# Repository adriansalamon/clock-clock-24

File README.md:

## My own ClockClock 24 replica

My own take/version of the ClockClock 24 by [Humans Since 1982](https://www.humanssince1982.com) - A digital clock made from 24 analog clocks.
All credit goes to them for coming up with such an awesome design.

My version is made 100% from scratch using my own hardware design.
Mine is also slightly smaller, made to fit perfectly on my shelf.
This design uses 6 Arduino nanos, each in control of 4 individual
clocks, and an ESP32 which orchestrates and sends commands to all
Arduinos.

The physical clock is made from MDF, which was routed using a 3d
printed jig (I don't own a CNC). That process will not be published.

The software is still WIP and not finished.

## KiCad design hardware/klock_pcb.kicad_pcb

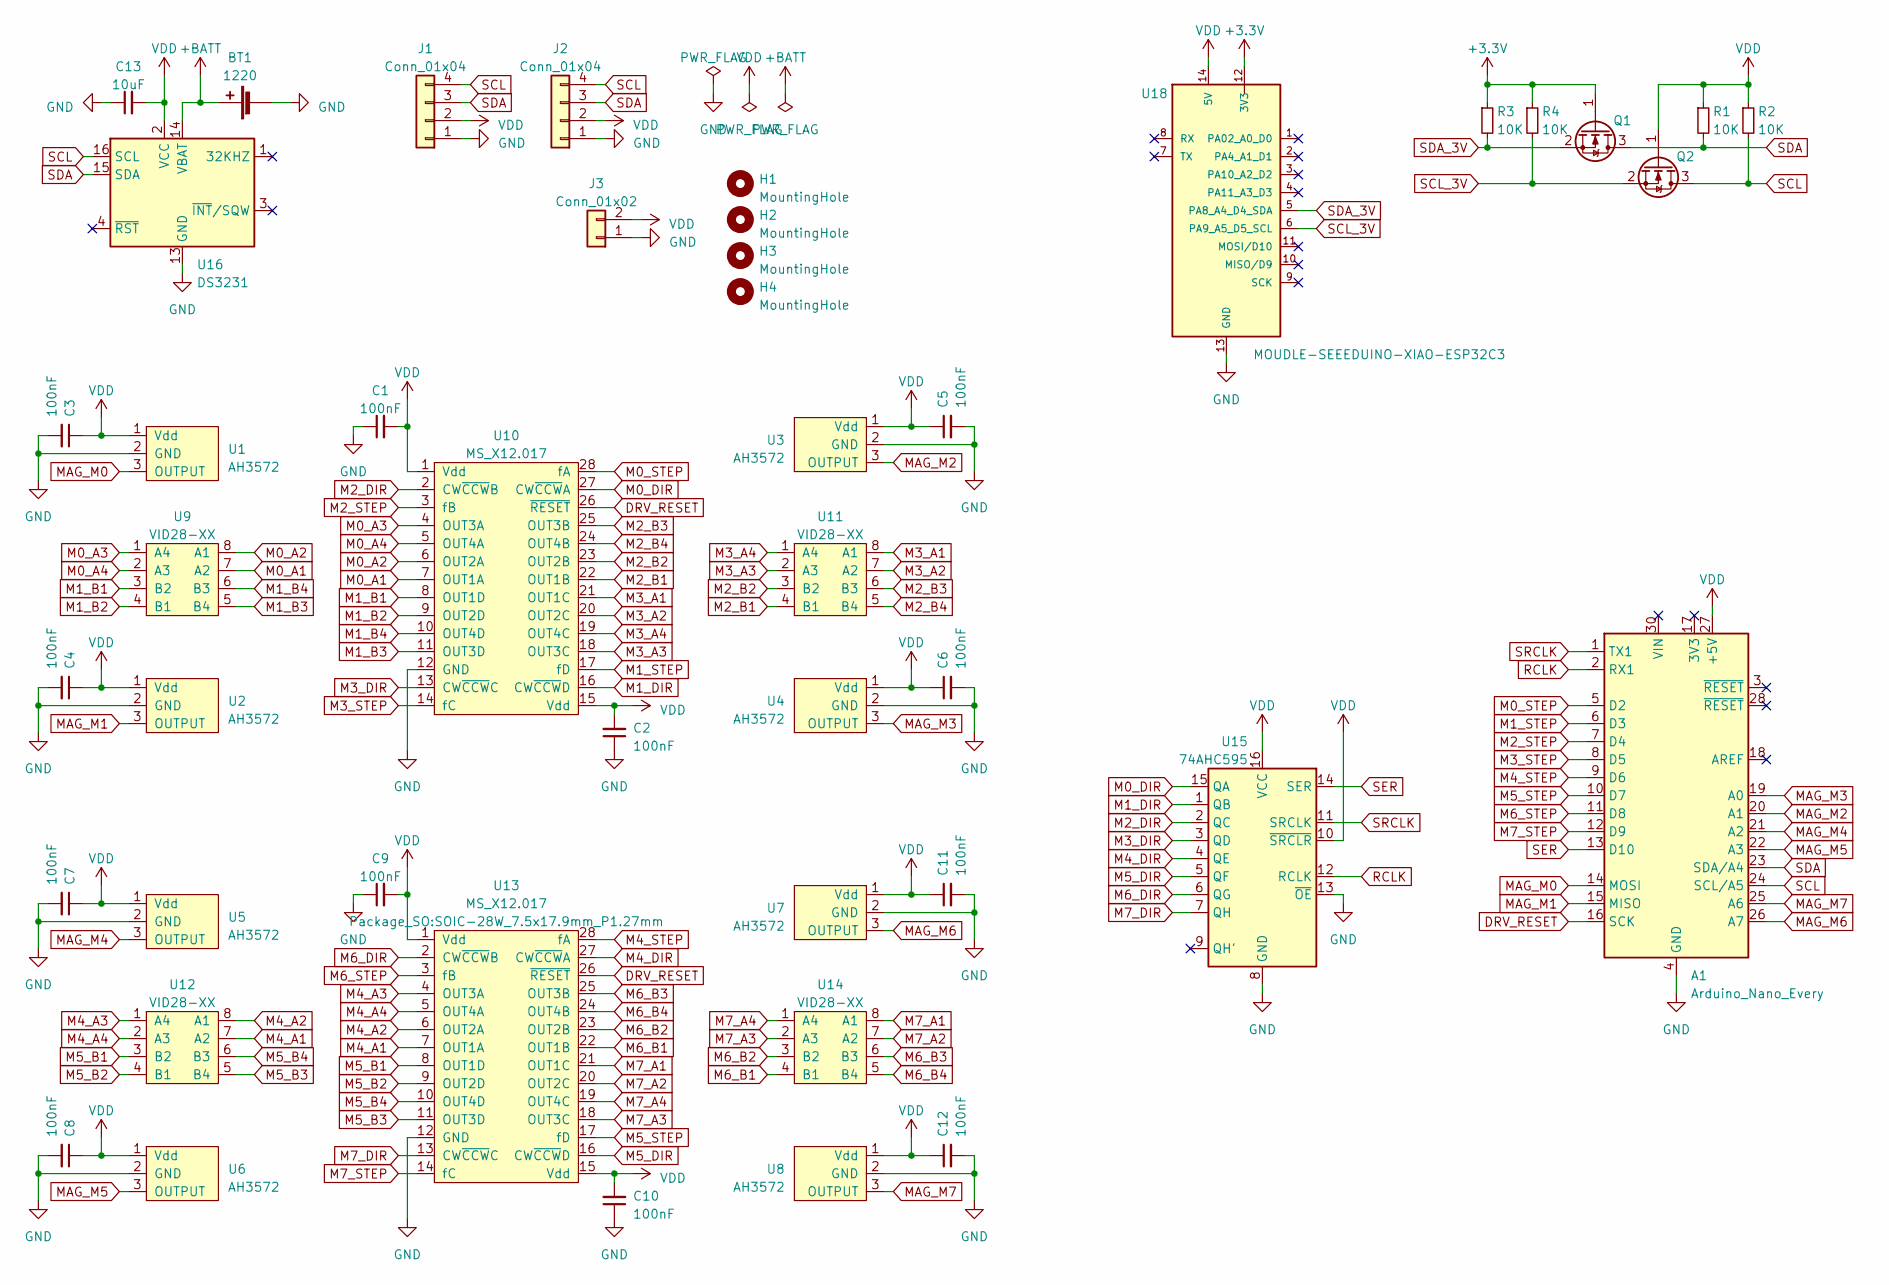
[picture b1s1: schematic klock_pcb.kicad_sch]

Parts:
A1: Arduino_Nano_Every; Arduino_Nano
BT1: 1220; BatteryHolder_Keystone_3001_1x12mm
C1, C2, C3, C4, C5, C6, C7, C8, C9, C10, C11, C12: 100nF; C_0805_2012Metric_Pad1.18x1.45mm_HandSolder
C13: 10uF; C_0805_2012Metric_Pad1.18x1.45mm_HandSolder
H1, H2, H3, H4: MountingHole; MountingHole_3.2mm_M3_Pad
J1, J2: Conn_01x04; JST_SH_SM04B-SRSS-TB_1x04-1MP_P1.00mm_Horizontal
J3: Conn_01x02; PinHeader_1x02_P2.54mm_Vertical
Q1, Q2: BSS138; SOT-23
R1, R2, R3, R4: 10K; R_0805_2012Metric_Pad1.20x1.40mm_HandSolder
U1, U2, U3, U4, U5, U6, U7, U8: AH3572; AH3572-SOT-23
U9, U11, U12, U14: VID28-XX; VID28-XX_DownMount
U10, U13: MS_X12.017; SOIC-28W_7.5x17.9mm_P1.27mm
U15: 74AHC595; DIP-16_W7.62mm
U16: DS3231; SOIC-16W_7.5x10.3mm_P1.27mm
U18: MOUDLE-SEEEDUINO-XIAO-ESP32C3; seeduino-MOUDLE14P-THT

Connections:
+3.3V: Q1.1 (G), R3.1, R4.1, U18.12 (3V3)
+BATT: BT1.1 (+), U16.14 (VBAT)
DRV_RESET: A1.16 (SCK), U10.26 (~RESET), U13.26 (~RESET)
GND: A1.4 (GND), A1.29 (GND), BT1.2 (-), C1.1, C2.1, C3.2, C4.2, C5.2, C6.2, C7.2, C8.2, C9.1, C10.1, C11.2, C12.2, C13.1, J1.1, J2.1, J3.1, U1.2 (GND), U2.2 (GND), U3.2 (GND), U4.2 (GND), U5.2 (GND), U6.2 (GND), U7.2 (GND), U8.2 (GND), U10.12 (GND), U13.12 (GND), U15.8 (GND), U15.13 (~OE), U16.5 (GND), U16.6 (GND), U16.7 (GND), U16.8 (GND), U16.9 (GND), U16.10 (GND), U16.11 (GND), U16.12 (GND), U16.13 (GND), U18.13 (GND)
M0_A1: U9.7 (A2), U10.7 (OUT1A)
M0_A2: U9.8 (A1), U10.6 (OUT2A)
M0_A3: U9.1 (A4), U10.4 (OUT3A)
M0_A4: U9.2 (A3), U10.5 (OUT4A)
M0_DIR: U10.27 (CW~CCWA), U15.15 (QA)
M0_STEP: A1.5 (D2), U10.28 (fA)
M1_B1: U9.3 (B2), U10.8 (OUT1D)
M1_B2: U9.4 (B1), U10.9 (OUT2D)
M1_B3: U9.5 (B4), U10.11 (OUT3D)
M1_B4: U9.6 (B3), U10.10 (OUT4D)
M1_DIR: U10.16 (CW~CCWD), U15.1 (QB)
M1_STEP: A1.6 (D3), U10.17 (fD)
M2_B1: U10.22 (OUT1B), U11.4 (B1)
M2_B2: U10.23 (OUT2B), U11.3 (B2)
M2_B3: U10.25 (OUT3B), U11.6 (B3)
M2_B4: U10.24 (OUT4B), U11.5 (B4)
M2_DIR: U10.2 (CW~CCWB), U15.2 (QC)
M2_STEP: A1.7 (D4), U10.3 (fB)
M3_A1: U10.21 (OUT1C), U11.8 (A1)
M3_A2: U10.20 (OUT2C), U11.7 (A2)
M3_A3: U10.18 (OUT3C), U11.2 (A3)
M3_A4: U10.19 (OUT4C), U11.1 (A4)
M3_DIR: U10.13 (CW~CCWC), U15.3 (QD)
M3_STEP: A1.8 (D5), U10.14 (fC)
M4_A1: U12.7 (A2), U13.7 (OUT1A)
M4_A2: U12.8 (A1), U13.6 (OUT2A)
M4_A3: U12.1 (A4), U13.4 (OUT3A)
M4_A4: U12.2 (A3), U13.5 (OUT4A)
M4_DIR: U13.27 (CW~CCWA), U15.4 (QE)
M4_STEP: A1.9 (D6), U13.28 (fA)
M5_B1: U12.3 (B2), U13.8 (OUT1D)
M5_B2: U12.4 (B1), U13.9 (OUT2D)
M5_B3: U12.5 (B4), U13.11 (OUT3D)
M5_B4: U12.6 (B3), U13.10 (OUT4D)
M5_DIR: U13.16 (CW~CCWD), U15.5 (QF)
M5_STEP: A1.10 (D7), U13.17 (fD)
M6_B1: U13.22 (OUT1B), U14.4 (B1)
M6_B2: U13.23 (OUT2B), U14.3 (B2)
M6_B3: U13.25 (OUT3B), U14.6 (B3)
M6_B4: U13.24 (OUT4B), U14.5 (B4)
M6_DIR: U13.2 (CW~CCWB), U15.6 (QG)
M6_STEP: A1.11 (D8), U13.3 (fB)
M7_A1: U13.21 (OUT1C), U14.8 (A1)
M7_A2: U13.20 (OUT2C), U14.7 (A2)
M7_A3: U13.18 (OUT3C), U14.2 (A3)
M7_A4: U13.19 (OUT4C), U14.1 (A4)
M7_DIR: U13.13 (CW~CCWC), U15.7 (QH)
M7_STEP: A1.12 (D9), U13.14 (fC)
MAG_M0: A1.14 (MOSI), U1.3 (OUTPUT)
MAG_M1: A1.15 (MISO), U2.3 (OUTPUT)
MAG_M2: A1.20 (A1), U3.3 (OUTPUT)
MAG_M3: A1.19 (A0), U4.3 (OUTPUT)
MAG_M4: A1.21 (A2), U5.3 (OUTPUT)
MAG_M5: A1.22 (A3), U6.3 (OUTPUT)
MAG_M6: A1.26 (A7), U7.3 (OUTPUT)
MAG_M7: A1.25 (A6), U8.3 (OUTPUT)
RCLK: A1.2 (RX1), U15.12 (RCLK)
SCL: A1.24 (SCL/A5), J1.4, J2.4, Q2.3 (D), R2.2, U16.16 (SCL)
SCL_3V: Q2.2 (S), R4.2, U18.6 (PA9_A5_D5_SCL)
SDA: A1.23 (SDA/A4), J1.3, J2.3, Q1.3 (D), R1.2, U16.15 (SDA)
SDA_3V: Q1.2 (S), R3.2, U18.5 (PA8_A4_D4_SDA)
SER: A1.13 (D10), U15.14 (SER)
SRCLK: A1.1 (TX1), U15.11 (SRCLK)
VDD: A1.27 (+5V), C1.2, C2.2, C3.1, C4.1, C5.1, C6.1, C7.1, C8.1, C9.2, C10.2, C11.1, C12.1, C13.2, J1.2, J2.2, J3.2, Q2.1 (G), R1.1, R2.1, U1.1 (Vdd), U2.1 (Vdd), U3.1 (Vdd), U4.1 (Vdd), U5.1 (Vdd), U6.1 (Vdd), U7.1 (Vdd), U8.1 (Vdd), U10.1 (Vdd), U10.15 (Vdd), U13.1 (Vdd), U13.15 (Vdd), U15.10 (~SRCLR), U15.16 (VCC), U16.2 (VCC), U18.14 (5V)

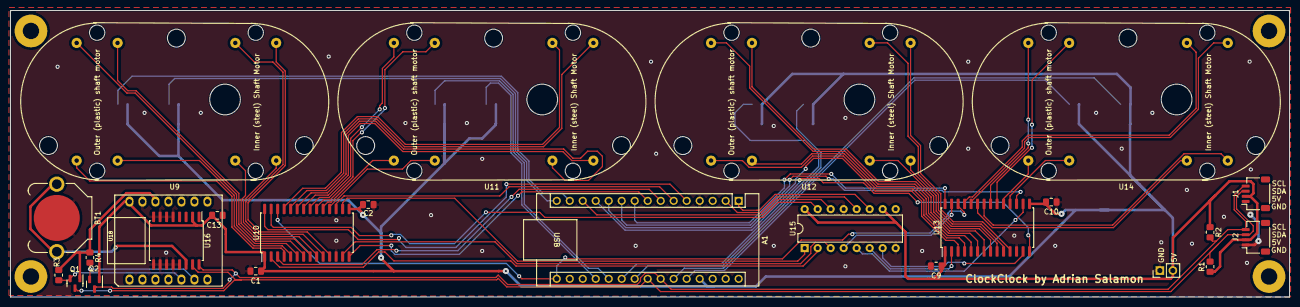
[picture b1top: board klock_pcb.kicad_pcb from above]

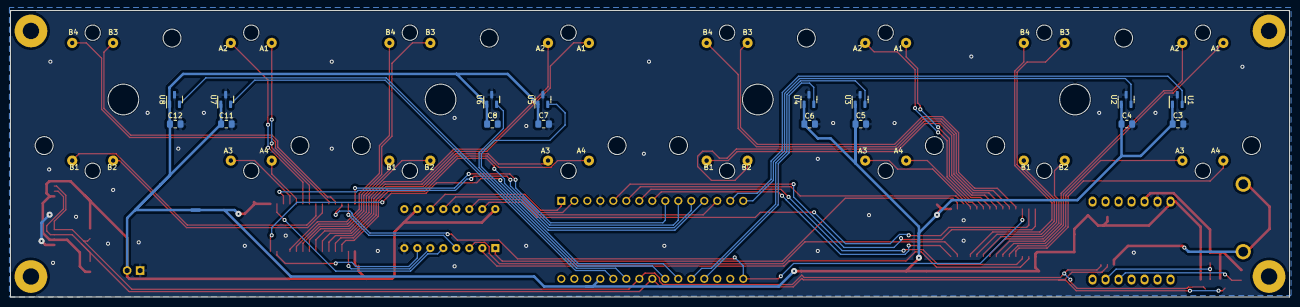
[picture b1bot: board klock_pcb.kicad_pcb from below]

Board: 2 copper layers, 250.0 x 56.0 mm, 45 parts (16 on the bottom side), 68 nets.

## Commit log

2023-03-23 Initial project
2023-03-24 working with i2c
2023-04-08 checkpoint :)
2023-08-12 initial implementation of modes
2024-12-01 add hardware files
2024-12-01 readme
2024-12-01 add license
2024-12-01 fix readme
2024-12-01 add vid
